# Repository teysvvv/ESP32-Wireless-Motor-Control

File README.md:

# ESP32-Wireless-Motor-Control
# Project Overview
This project involves developing a wireless control and power supply system for a manual slope-climbing robot designed to travel from one edge of an inclined surface to the other. 

The system uses two **ESP32-DevKitC-32UE**. The first ESP32 is connected to a Funduino joystick shield, which collects user inputs and transmits them wirelessly through ESP-NOW. The second ESP32, mounted on the robot, receives these commands and communicates with the motor controllers through CAN using an MCP2515 module.

The robot is powered by a **4S battery**. To provide a regulated power supply for the ESP32, I designed a custom PCB incorporating two voltage regulation stages:

- **LM2596S-5:** Steps down the battery voltage to a regulated 5 V.
- **AMS1117-3.3:** Further regulates the 5 V supply to a stable 3.3 V for the ESP32.

## System Architecture

1. **Transmitter:** The first ESP32 reads joystick and button inputs through the Funduino joystick shield.
2. **Wireless Communication:** ESP-NOW transmits control data between the two ESP32 boards.
3. **Receiver:** The second ESP32 receives the commands and communicates with the motor controllers through the MCP2515 CAN module.
4. **Motor Control:**
   - Motor 1: Speed control with encoder feedback and position holding.
   - Motor 2: Steering position control.

## Software and Tools

- C++ / Arduino IDE
- ESP-NOW
- CAN communication
- KiCad

## Project Status

Under development and hardware testing.

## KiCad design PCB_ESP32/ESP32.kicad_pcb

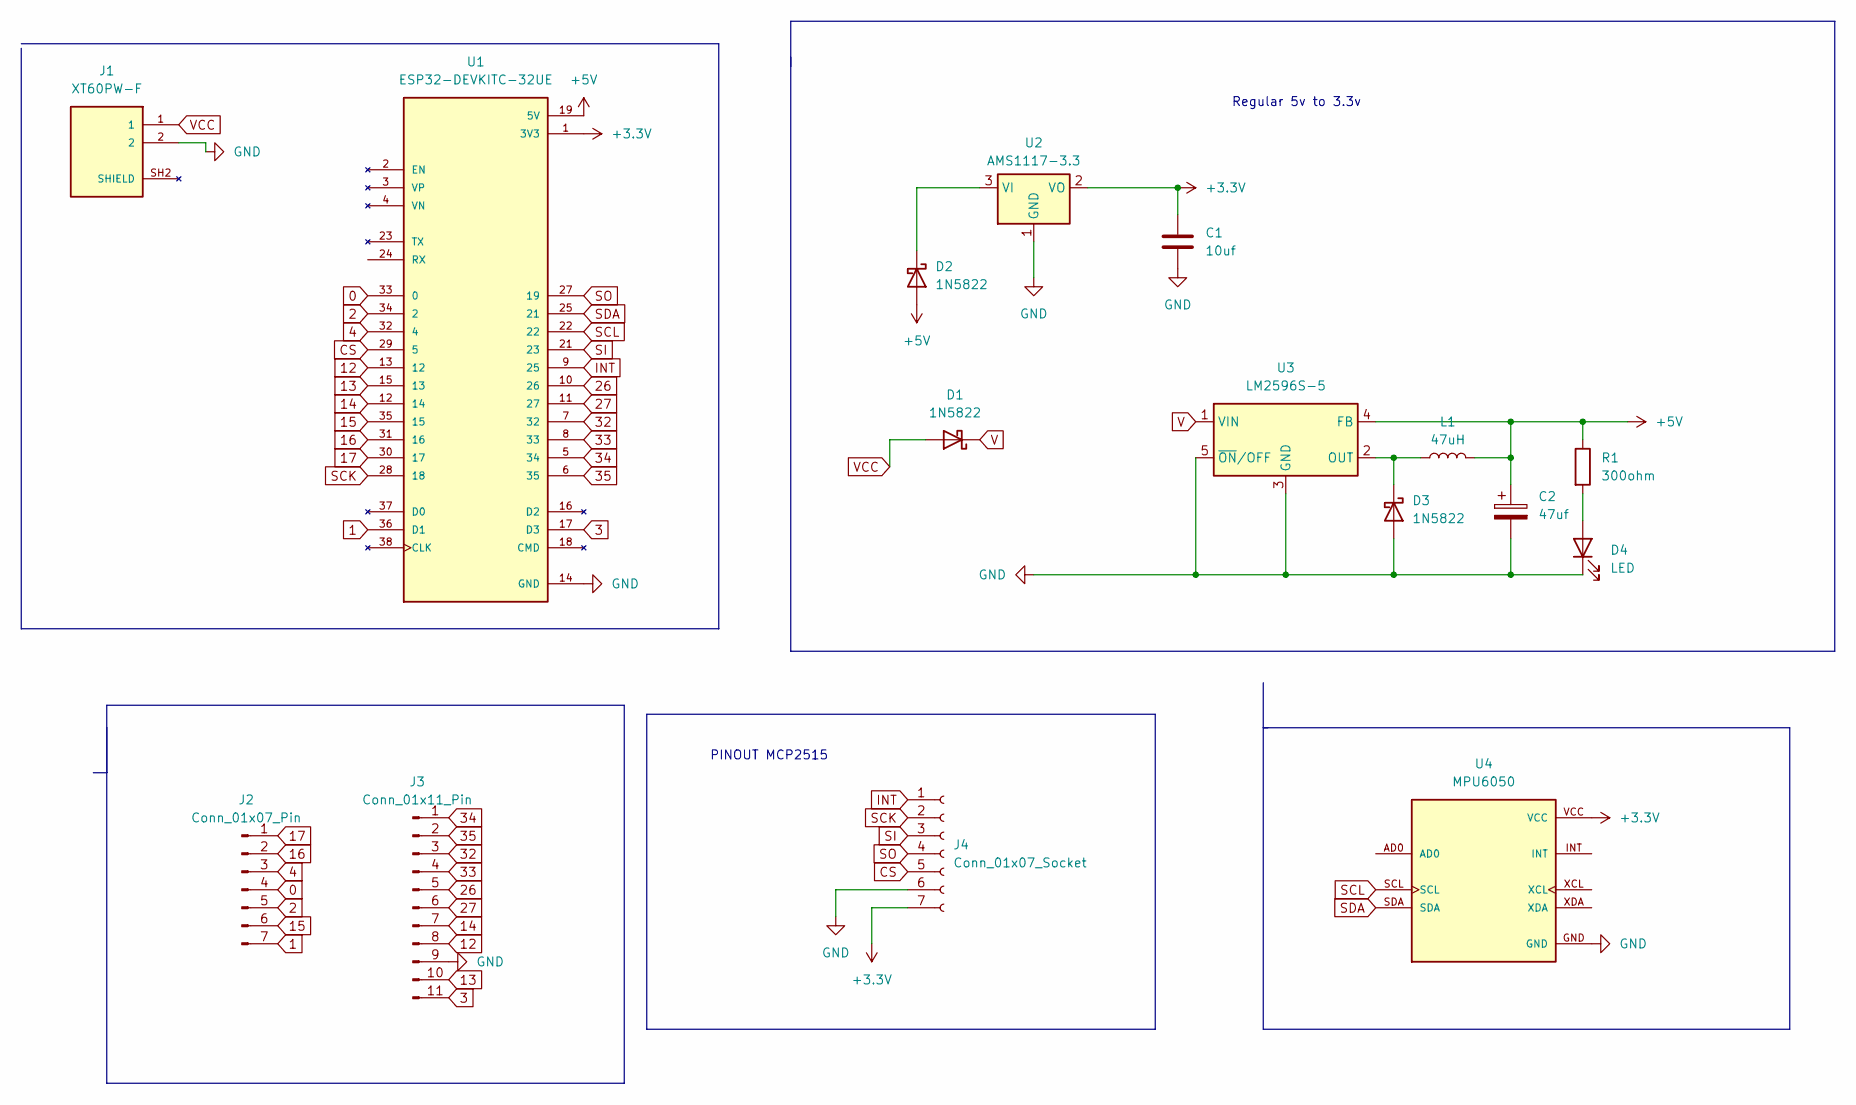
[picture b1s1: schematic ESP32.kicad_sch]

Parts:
C1: 10uf; C_0603_1608Metric
C2: 47uf; CP_Radial_D6.3mm_P2.50mm
D1, D2, D3: 1N5822; D_SMA
D4: LED; LED_D5.0mm
J1: XT60PW-F; AMASS_XT60PW-F; PARTREV 1.2
J2: Conn_01x07_Pin; PinHeader_1x07_P2.00mm_Vertical
J3: Conn_01x11_Pin; PinHeader_1x11_P2.54mm_Vertical
J4: Conn_01x07_Socket; PinSocket_1x07_P2.54mm_Vertical
L1: 47uH; L_Wuerth_HCI-7030
R1: 300ohm; R_0603_1608Metric
U1: ESP32-DEVKITC-32UE; ESPRESSIF_ESP32-DEVKITC-32UE; PARTREV V4
U2: AMS1117-3.3; SOT-223-3_TabPin2
U3: LM2596S-5; TO-263-5_TabPin3
U4: MPU6050; MODULE_OC09600; PARTREV NA

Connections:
0: J2.4, U1.33 (0)
1: J2.7, U1.36 (D1)
2: J2.5, U1.34 (2)
3: J3.11, U1.17 (D3)
4: J2.3, U1.32 (4)
12: J3.8, U1.13 (12)
13: J3.10, U1.15 (13)
14: J3.7, U1.12 (14)
15: J2.6, U1.35 (15)
16: J2.2, U1.31 (16)
17: J2.1, U1.30 (17)
26: J3.5, U1.10 (26)
27: J3.6, U1.11 (27)
32: J3.3, U1.7 (32)
33: J3.4, U1.8 (33)
34: J3.1, U1.5 (34)
35: J3.2, U1.6 (35)
+3.3V: C1.1, J4.7, U1.1 (3V3), U2.2 (VO), U4.VCC
+5V: C2.1, D2.2 (A), L1.2, R1.1, U1.19 (5V), U3.4 (FB)
CS: J4.5, U1.29 (5)
GND: C1.2, C2.2, D3.2 (A), D4.1 (K), J1.2, J3.9, J4.6, U1.14 (GND), U1.20 (GND), U1.26 (GND), U2.1 (GND), U3.3 (GND), U3.5 (~ON/OFF), U4.GND
INT: J4.1, U1.9 (25)
unnamed: D2.1 (K), U2.3 (VI)
unnamed: D4.2 (A), R1.2
SCK: J4.2, U1.28 (18)
SCL: U1.22, U4.SCL
SDA: U1.25 (21), U4.SDA
SI: J4.3, U1.21 (23)
SO: J4.4, U1.27 (19)
VCC: D1.2 (A), J1.1

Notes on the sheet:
PINOUT MCP2515
Regular 5v to 3.3v

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
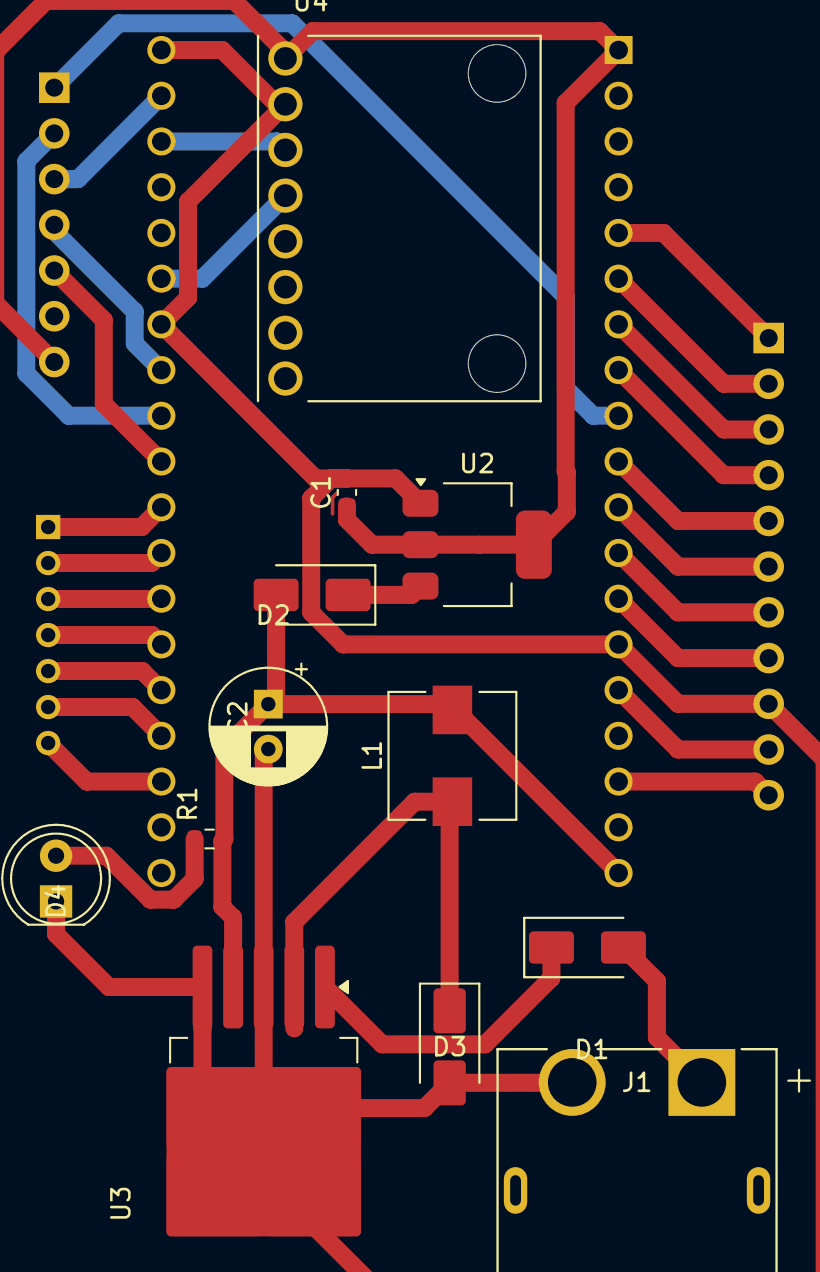
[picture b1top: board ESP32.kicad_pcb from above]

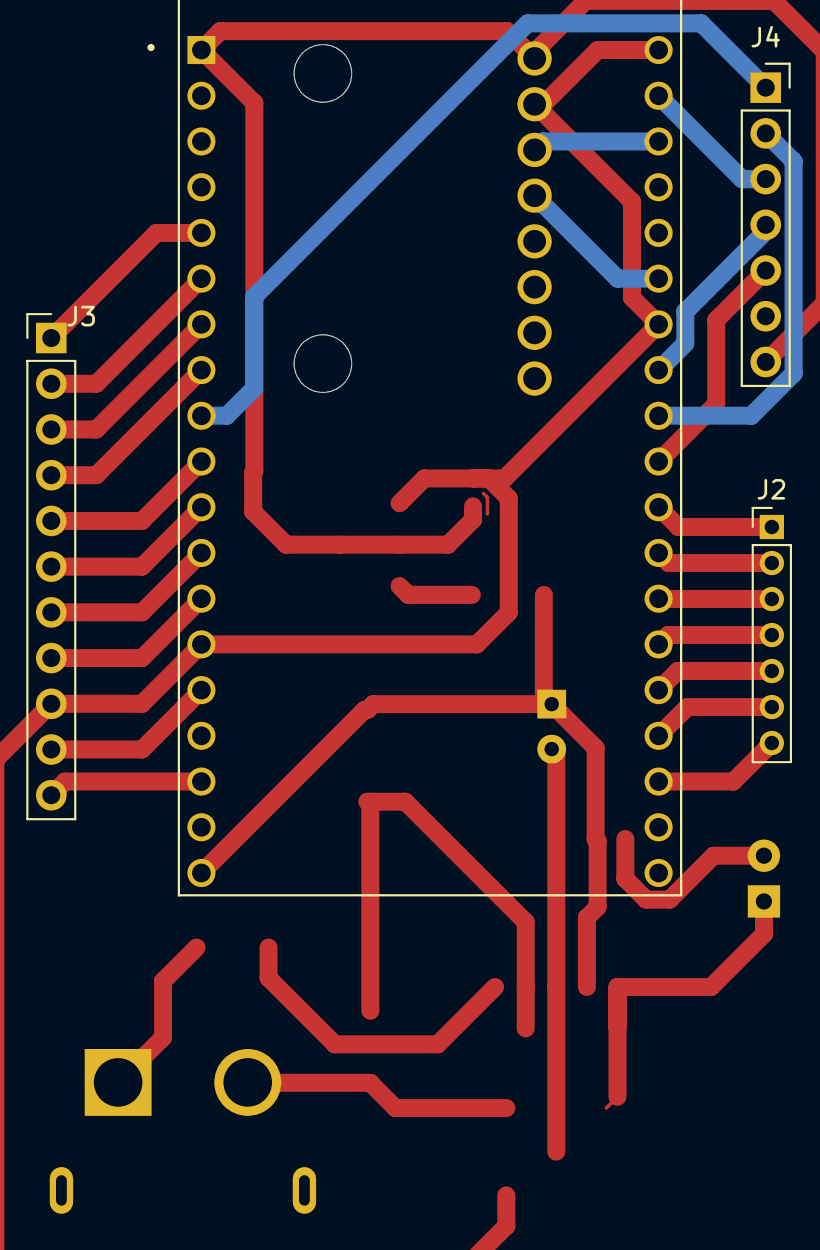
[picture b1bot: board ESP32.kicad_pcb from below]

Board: 2 copper layers, 16 parts (4 on the bottom side), 31 nets.
